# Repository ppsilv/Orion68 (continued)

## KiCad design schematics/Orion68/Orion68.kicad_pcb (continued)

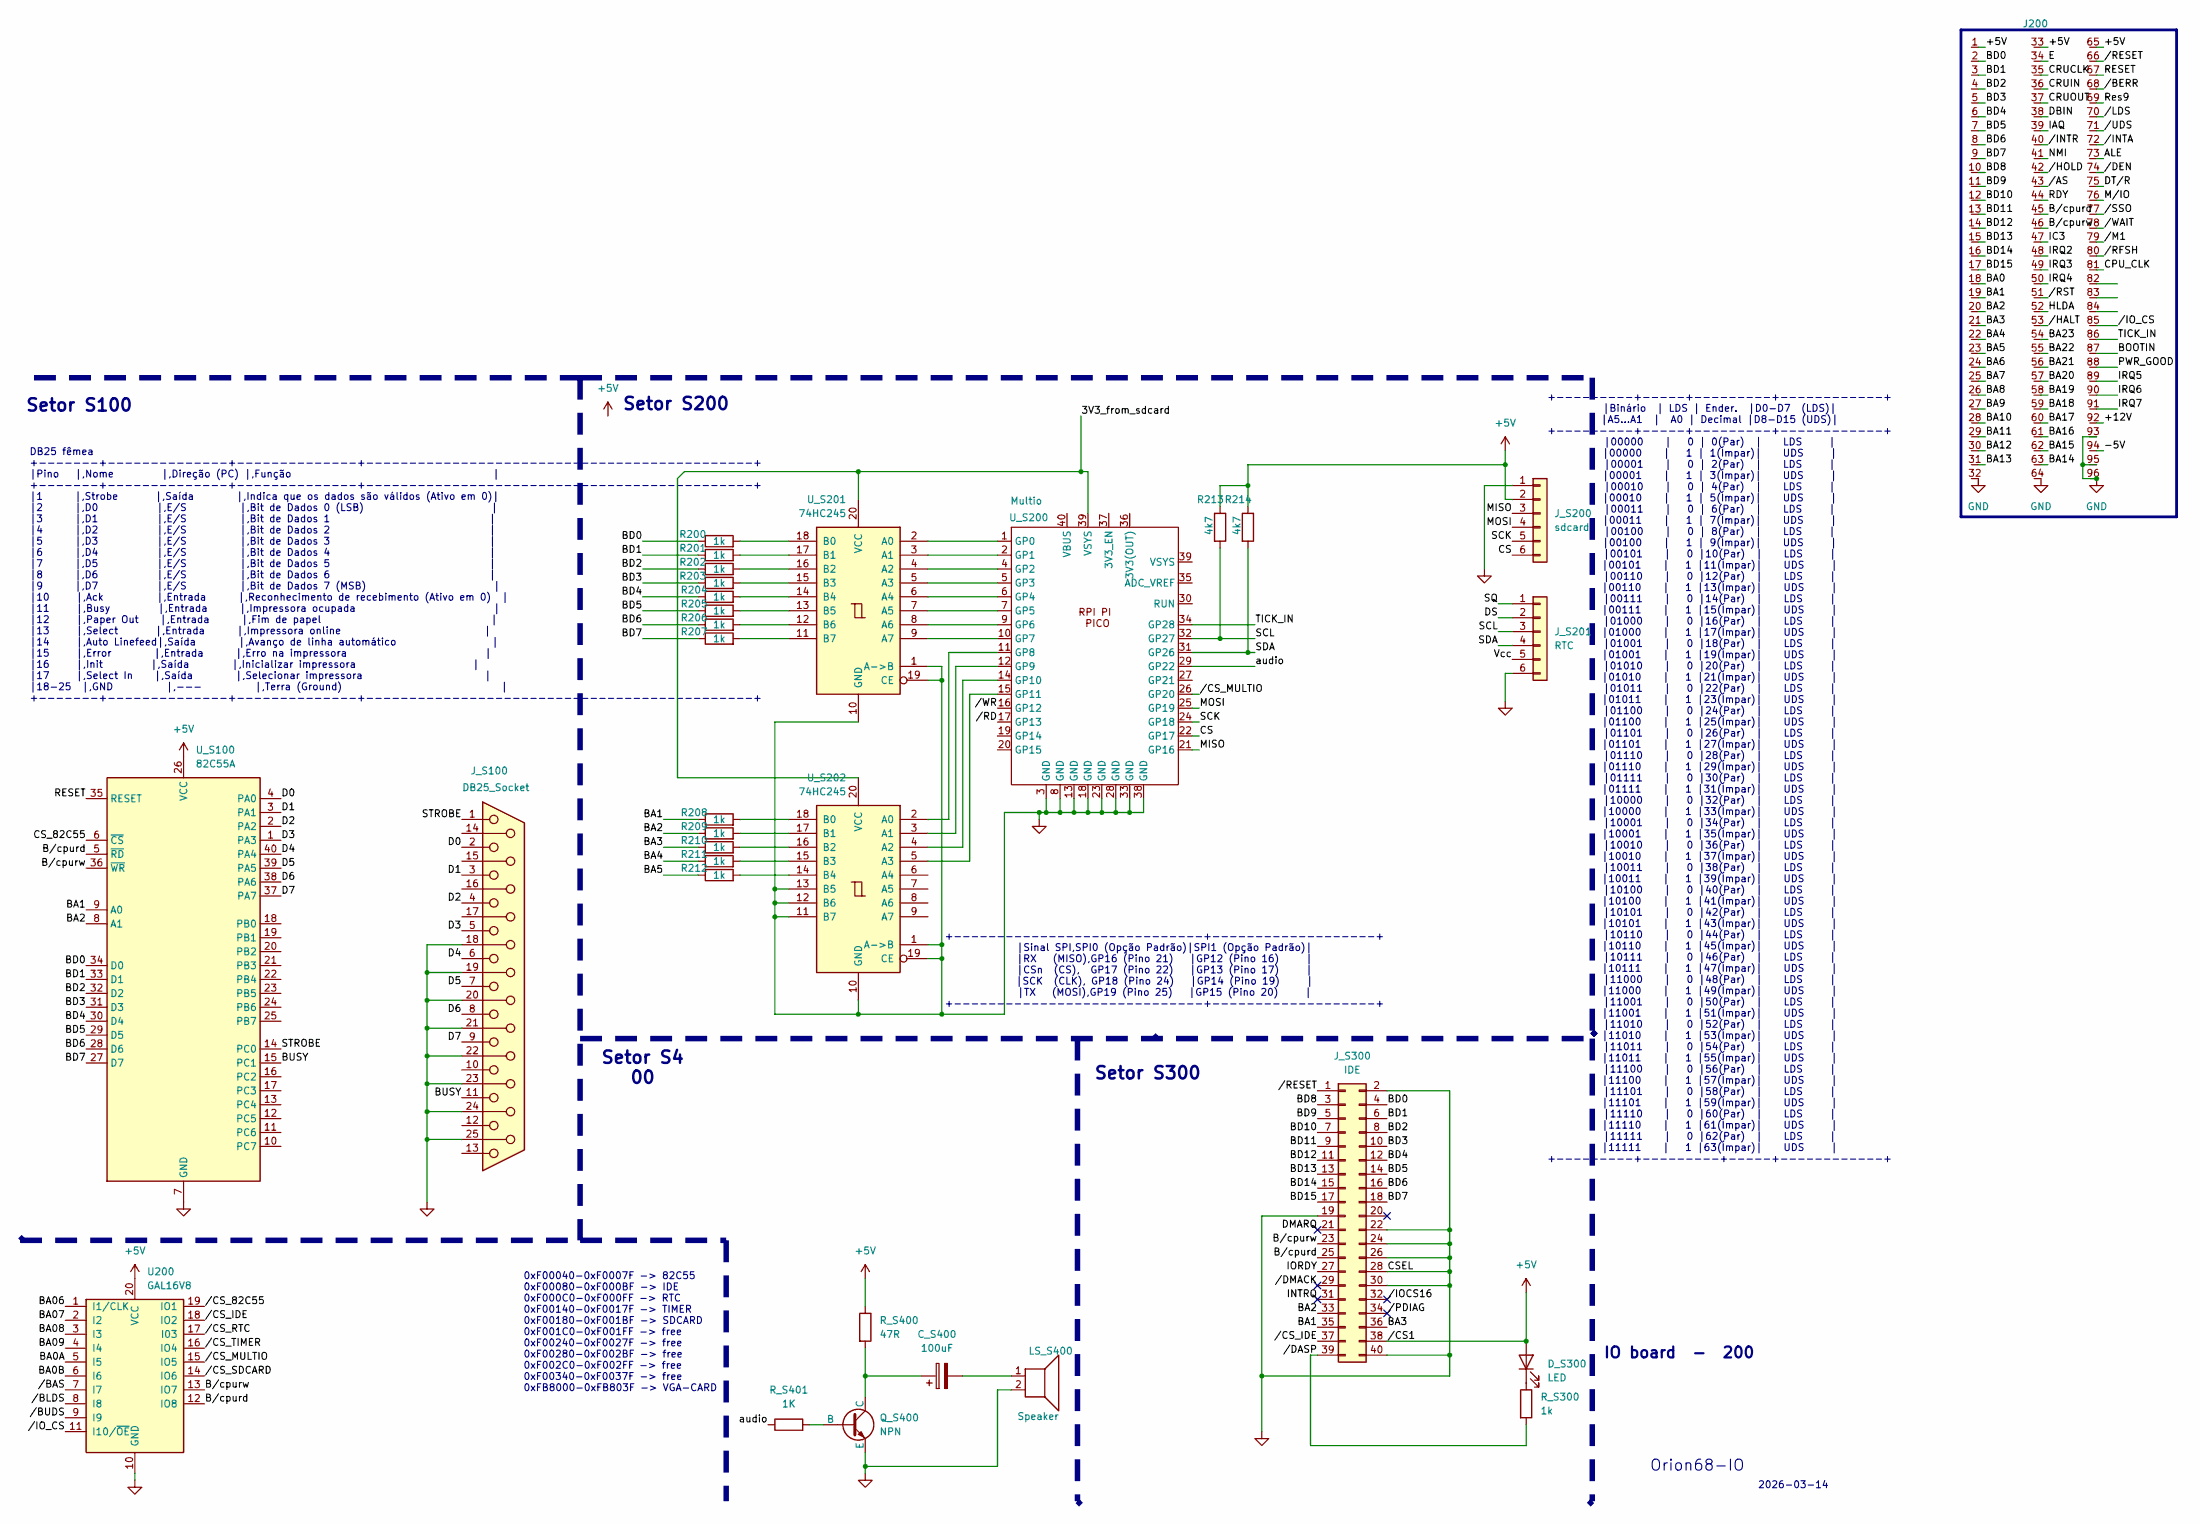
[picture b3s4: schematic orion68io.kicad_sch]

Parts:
C_S400: 100uF; CP_Radial_D5.0mm_P2.50mm
D_S300: LED; D_T-1_P5.08mm_Horizontal
J200: Euro96pin; conn_euro96
J_S100: DB25_Socket; PinHeader_2x13_P2.54mm_Vertical
J_S200: sdcard; PinSocket_1x06_P2.54mm_Vertical
J_S201: RTC; PinSocket_1x06_P2.54mm_Vertical
J_S300: IDE; PinHeader_2x20_P2.54mm_Horizontal
LS_S400: Speaker; PinHeader_1x02_P2.54mm_Vertical
Q_S400: NPN; TO-92L_Inline
R200, R201, R202, R203, R204, R205, R206, R207, R208, R209, R210, R211, R212: 1k; R_Axial_DIN0204_L3.6mm_D1.6mm_P5.08mm_Horizontal
R213, R214: 4k7; R_Axial_DIN0204_L3.6mm_D1.6mm_P5.08mm_Horizontal
R_S300: 1k; R_Axial_DIN0204_L3.6mm_D1.6mm_P5.08mm_Horizontal
R_S400: 47R; R_Axial_DIN0204_L3.6mm_D1.6mm_P5.08mm_Horizontal
R_S401: 1K; R_Axial_DIN0204_L3.6mm_D1.6mm_P5.08mm_Horizontal
U200: GAL16V8; DIP-20_W7.62mm
U_S100: 82C55A; DIP-40_W15.24mm
U_S200: Multio; DIP-40_W15.24mm
U_S201, U_S202: 74HC245; DIP-20_W7.62mm

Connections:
+5V: D_S300.2 (A), J200.1, J200.33, J200.65, J_S200.2, J_S300.38, R213.1, R214.1, R_S400.1, U200.20 (VCC), U_S100.26 (VCC); also elsewhere on the board
/Orion68-IO/3V3_from_sdcard: U_S200.39 (VSYS), U_S201.20 (VCC), U_S202.20 (VCC)
/Orion68-IO/+12V: J200.92
/Orion68-IO/-5V: J200.94
/Orion68-IO/ALE: J200.73
/Orion68-IO/BA0: J200.18
/Orion68-IO/BA0A: U200.5 (I5)
/Orion68-IO/BA0B: U200.6 (I6)
/Orion68-IO/BA1: J200.19, J_S300.35, R208.1, U_S100.9 (A0)
/Orion68-IO/BA2: J200.20, J_S300.33, R209.1, U_S100.8 (A1)
/Orion68-IO/BA3: J200.21, J_S300.36, R210.1
/Orion68-IO/BA4: J200.22, R211.1
/Orion68-IO/BA5: J200.23, R212.1
/Orion68-IO/BA06: U200.1 (I1/CLK)
/Orion68-IO/BA6: J200.24
/Orion68-IO/BA07: U200.2 (I2)
/Orion68-IO/BA7: J200.25
/Orion68-IO/BA08: U200.3 (I3)
/Orion68-IO/BA8: J200.26
/Orion68-IO/BA09: U200.4 (I4)
/Orion68-IO/BA9: J200.27
/Orion68-IO/BA10: J200.28
/Orion68-IO/BA11: J200.29
/Orion68-IO/BA12: J200.30
/Orion68-IO/BA13: J200.31
/Orion68-IO/BA14: J200.63
/Orion68-IO/BA15: J200.62
/Orion68-IO/BA16: J200.61
/Orion68-IO/BA17: J200.60
/Orion68-IO/BA18: J200.59
/Orion68-IO/BA19: J200.58
/Orion68-IO/BA20: J200.57
/Orion68-IO/BA21: J200.56
/Orion68-IO/BA22: J200.55
/Orion68-IO/BA23: J200.54
/Orion68-IO/BD0: J200.2, J_S300.4, R200.1, U_S100.34 (D0)
/Orion68-IO/BD1: J200.3, J_S300.6, R201.1, U_S100.33 (D1)
/Orion68-IO/BD2: J200.4, J_S300.8, R202.1, U_S100.32 (D2)
/Orion68-IO/BD3: J200.5, J_S300.10, R203.1, U_S100.31 (D3)
/Orion68-IO/BD4: J200.6, J_S300.12, R204.1, U_S100.30 (D4)
/Orion68-IO/BD5: J200.7, J_S300.14, R205.1, U_S100.29 (D5)
/Orion68-IO/BD6: J200.8, J_S300.16, R206.1, U_S100.28 (D6)
/Orion68-IO/BD7: J200.9, J_S300.18, R207.1, U_S100.27 (D7)
/Orion68-IO/BD8: J200.10, J_S300.3
/Orion68-IO/BD9: J200.11, J_S300.5
/Orion68-IO/BD10: J200.12, J_S300.7
/Orion68-IO/BD11: J200.13, J_S300.9
/Orion68-IO/BD12: J200.14, J_S300.11
/Orion68-IO/BD13: J200.15, J_S300.13
/Orion68-IO/BD14: J200.16, J_S300.15
/Orion68-IO/BD15: J200.17, J_S300.17
/Orion68-IO/BOOTIN: J200.87
/Orion68-IO/BUSY: J_S100.11, U_S100.15 (PC1)
/Orion68-IO/B/cpurd: J200.45, J_S300.25, U200.12 (IO8), U_S100.5 (~RD)
/Orion68-IO/B/cpurw: J200.46, J_S300.23, U200.13 (IO7), U_S100.36 (~WR)
/Orion68-IO/CPU_CLK: J200.81
/Orion68-IO/CRUCLK: J200.35
/Orion68-IO/CRUIN: J200.36
/Orion68-IO/CRUOUT: J200.37
/Orion68-IO/CS: J_S200.6, U_S200.22 (GP17)
/Orion68-IO/CS_82C55: U_S100.6 (~CS)
/Orion68-IO/D0: J_S100.2, U_S100.4 (PA0)
/Orion68-IO/D1: J_S100.3, U_S100.3 (PA1)
/Orion68-IO/D2: J_S100.4, U_S100.2 (PA2)
/Orion68-IO/D3: J_S100.5, U_S100.1 (PA3)
/Orion68-IO/D4: J_S100.6, U_S100.40 (PA4)
/Orion68-IO/D5: J_S100.7, U_S100.39 (PA5)
/Orion68-IO/D6: J_S100.8, U_S100.38 (PA6)
/Orion68-IO/D7: J_S100.9, U_S100.37 (PA7)
/Orion68-IO/DBIN: J200.38
/Orion68-IO/DMARQ: J_S300.21
/Orion68-IO/DS: J_S201.2
/Orion68-IO/DT/R: J200.75
/Orion68-IO/E: J200.34
/Orion68-IO/HLDA: J200.52
/Orion68-IO/IAQ: J200.39
/Orion68-IO/IC3: J200.47
/Orion68-IO/INTRQ: J_S300.31
/Orion68-IO/IORDY: J_S300.27
/Orion68-IO/IRQ2: J200.48
/Orion68-IO/IRQ3: J200.49
/Orion68-IO/IRQ4: J200.50
/Orion68-IO/IRQ5: J200.89
/Orion68-IO/IRQ6: J200.90
/Orion68-IO/IRQ7: J200.91
/Orion68-IO/MISO: J_S200.3, U_S200.21 (GP16)
/Orion68-IO/MOSI: J_S200.4, U_S200.25 (GP19)
/Orion68-IO/M/IO: J200.76
/Orion68-IO/NMI: J200.41
/Orion68-IO/PWR_GOOD: J200.88
/Orion68-IO/RDY: J200.44
/Orion68-IO/RESET: J200.67, U_S100.35 (RESET)
/Orion68-IO/Res9: J200.69
/Orion68-IO/SCK: J_S200.5, U_S200.24 (GP18)
/Orion68-IO/SCL: J_S201.3, R213.2, U_S200.32 (GP27)
/Orion68-IO/SDA: J_S201.4, R214.2, U_S200.31 (GP26)
/Orion68-IO/SQ: J_S201.1
/Orion68-IO/STROBE: J_S100.1, U_S100.14 (PC0)
/Orion68-IO/TICK_IN: J200.86, U_S200.34 (GP28)
/Orion68-IO/Vcc: J_S201.5
/Orion68-IO/audio: R_S401.1, U_S200.29 (GP22)
/Orion68-IO//AS: J200.43
/Orion68-IO//BAS: U200.7 (I7)
/Orion68-IO//BERR: J200.68
/Orion68-IO//BLDS: U200.8 (I8)
/Orion68-IO//BUDS: U200.9 (I9)
/Orion68-IO//CS_82C55: U200.19 (IO1)
/Orion68-IO//CS_IDE: J_S300.37, U200.18 (IO2)
/Orion68-IO//CS_MULTIO: U200.15 (IO5), U_S200.26 (GP20)
/Orion68-IO//CS_RTC: U200.17 (I03)
/Orion68-IO//CS_SDCARD: U200.14 (IO6)
/Orion68-IO//CS_TIMER: U200.16 (IO4)
/Orion68-IO//DASP: J_S300.39, R_S300.2
/Orion68-IO//DEN: J200.74
/Orion68-IO//DMACK: J_S300.29
/Orion68-IO//HALT: J200.53
/Orion68-IO//HOLD: J200.42
/Orion68-IO//INTA: J200.72
/Orion68-IO//INTR: J200.40
/Orion68-IO//IOCS16: J_S300.32
/Orion68-IO//IO_CS: J200.85, U200.11 (I10/~OE)
/Orion68-IO//LDS: J200.70
/Orion68-IO//M1: J200.79
/Orion68-IO//PDIAG: J_S300.34
/Orion68-IO//RD: U_S200.17 (GP13)
/Orion68-IO//RESET: J200.66, J_S300.1
/Orion68-IO//RFSH: J200.80
/Orion68-IO//RST: J200.51
/Orion68-IO//SSO: J200.77
/Orion68-IO//UDS: J200.71
/Orion68-IO//WAIT: J200.78
/Orion68-IO//WR: U_S200.16 (GP12)
GND: J200.32, J200.64, J200.93, J200.95, J200.96, J_S100.18, J_S100.19, J_S100.20, J_S100.21, J_S100.22, J_S100.23, J_S100.24, J_S100.25, J_S200.1, J_S201.6, J_S300.2, J_S300.19, J_S300.22, J_S300.24, J_S300.26, J_S300.28, J_S300.30, J_S300.40, LS_S400.2, Q_S400.3 (E), U200.10 (GND), U_S100.7 (GND), U_S200.3 (GND), U_S200.8 (GND), U_S200.13 (GND), U_S200.18 (GND), U_S200.23 (GND), U_S200.28 (GND), U_S200.33 (GND), U_S200.38 (GND), U_S201.1 (A->B), U_S201.10 (GND), U_S201.19 (CE), U_S202.1 (A->B), U_S202.10 (GND), U_S202.11 (B7), U_S202.12 (B6), U_S202.13 (B5), U_S202.19 (CE); also elsewhere on the board
unnamed: C_S400.2, LS_S400.1
unnamed: D_S300.1 (K), R_S300.1
unnamed: Q_S400.2 (B), R_S401.2
unnamed: C_S400.1, Q_S400.1 (C), R_S400.2
unnamed: U_S200.1 (GP0), U_S201.2 (A0)
unnamed: U_S200.2 (GP1), U_S201.3 (A1)
unnamed: U_S200.4 (GP2), U_S201.4 (A2)
unnamed: U_S200.5 (GP3), U_S201.5 (A3)
unnamed: U_S200.6 (GP4), U_S201.6 (A4)
unnamed: U_S200.7 (GP5), U_S201.7 (A5)
unnamed: U_S200.9 (GP6), U_S201.8 (A6)
unnamed: U_S200.10 (GP7), U_S201.9 (A7)
unnamed: U_S200.11 (GP8), U_S202.2 (A0)
unnamed: U_S200.12 (GP9), U_S202.3 (A1)
unnamed: U_S200.14 (GP10), U_S202.4 (A2)
unnamed: U_S200.15 (GP11), U_S202.5 (A3)
unnamed: R200.2, U_S201.18 (B0)
unnamed: R201.2, U_S201.17 (B1)
unnamed: R202.2, U_S201.16 (B2)
unnamed: R203.2, U_S201.15 (B3)
unnamed: R204.2, U_S201.14 (B4)
unnamed: R205.2, U_S201.13 (B5)
unnamed: R206.2, U_S201.12 (B6)
unnamed: R207.2, U_S201.11 (B7)
unnamed: R208.2, U_S202.18 (B0)
unnamed: R209.2, U_S202.17 (B1)
unnamed: R210.2, U_S202.16 (B2)
unnamed: R211.2, U_S202.15 (B3)
unnamed: R212.2, U_S202.14 (B4)

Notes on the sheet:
2026-03-14
Setor S4 00
+---------+-----+---------+------------+ |Binário | LDS | Ender. |D0-D7 (LDS)| |A5...A1 | A0 | Decimal |D8-D15 (UDS)| +---------+-----+---------+------------+ |00000 | 0 | 0(Par) | LDS | |00000 | 1 | 1(Ímpar)| UDS | |00001 | 0 | 2(Par) | LDS | |00001 | 1 | 3(Ímpar)| UDS | |00010 | 0 | 4(Par) | LDS 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
DB25 fêmea +-------+--------------+--------------+---------------------------------------------+ |Pino |,Nome |,Direção (PC) |,Função | +-------+--------------+--------------+---------------------------------------------+ |1 |,Strobe |,Saída |,Indica que os dados são válidos (Ativo em 0)| |2 |,D0 |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
IO board - 200
Orion68-IO
Setor S100
Setor S200
0xF00040-0xF0007F -> 82C55 0xF00080-0xF000BF -> IDE 0xF000C0-0xF000FF -> RTC 0xF00140-0xF0017F -> TIMER 0xF00180-0xF001BF -> SDCARD 0xF001C0-0xF001FF -> free 0xF00240-0xF0027F -> free 0xF00280-0xF002BF -> free 0xF002C0-0xF002FF -> free 0xF00340-0xF0037F -> free 0xFB8000-0xFB803F -> VGA-CARD
+-----------------------------+-------------------+ |Sinal SPI,SPI0 (Opção Padrão)|SPI1 (Opção Padrão)| |RX (MISO),GP16 (Pino 21) |GP12 (Pino 16) | |CSn (CS), GP17 (Pino 22) |GP13 (Pino 17) | |SCK (CLK), GP18 (Pino 24) |GP14 (Pino 19) | |TX (MOSI),GP19 (Pino 25) |GP15 (Pino 20) | +-----------------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
Setor S300

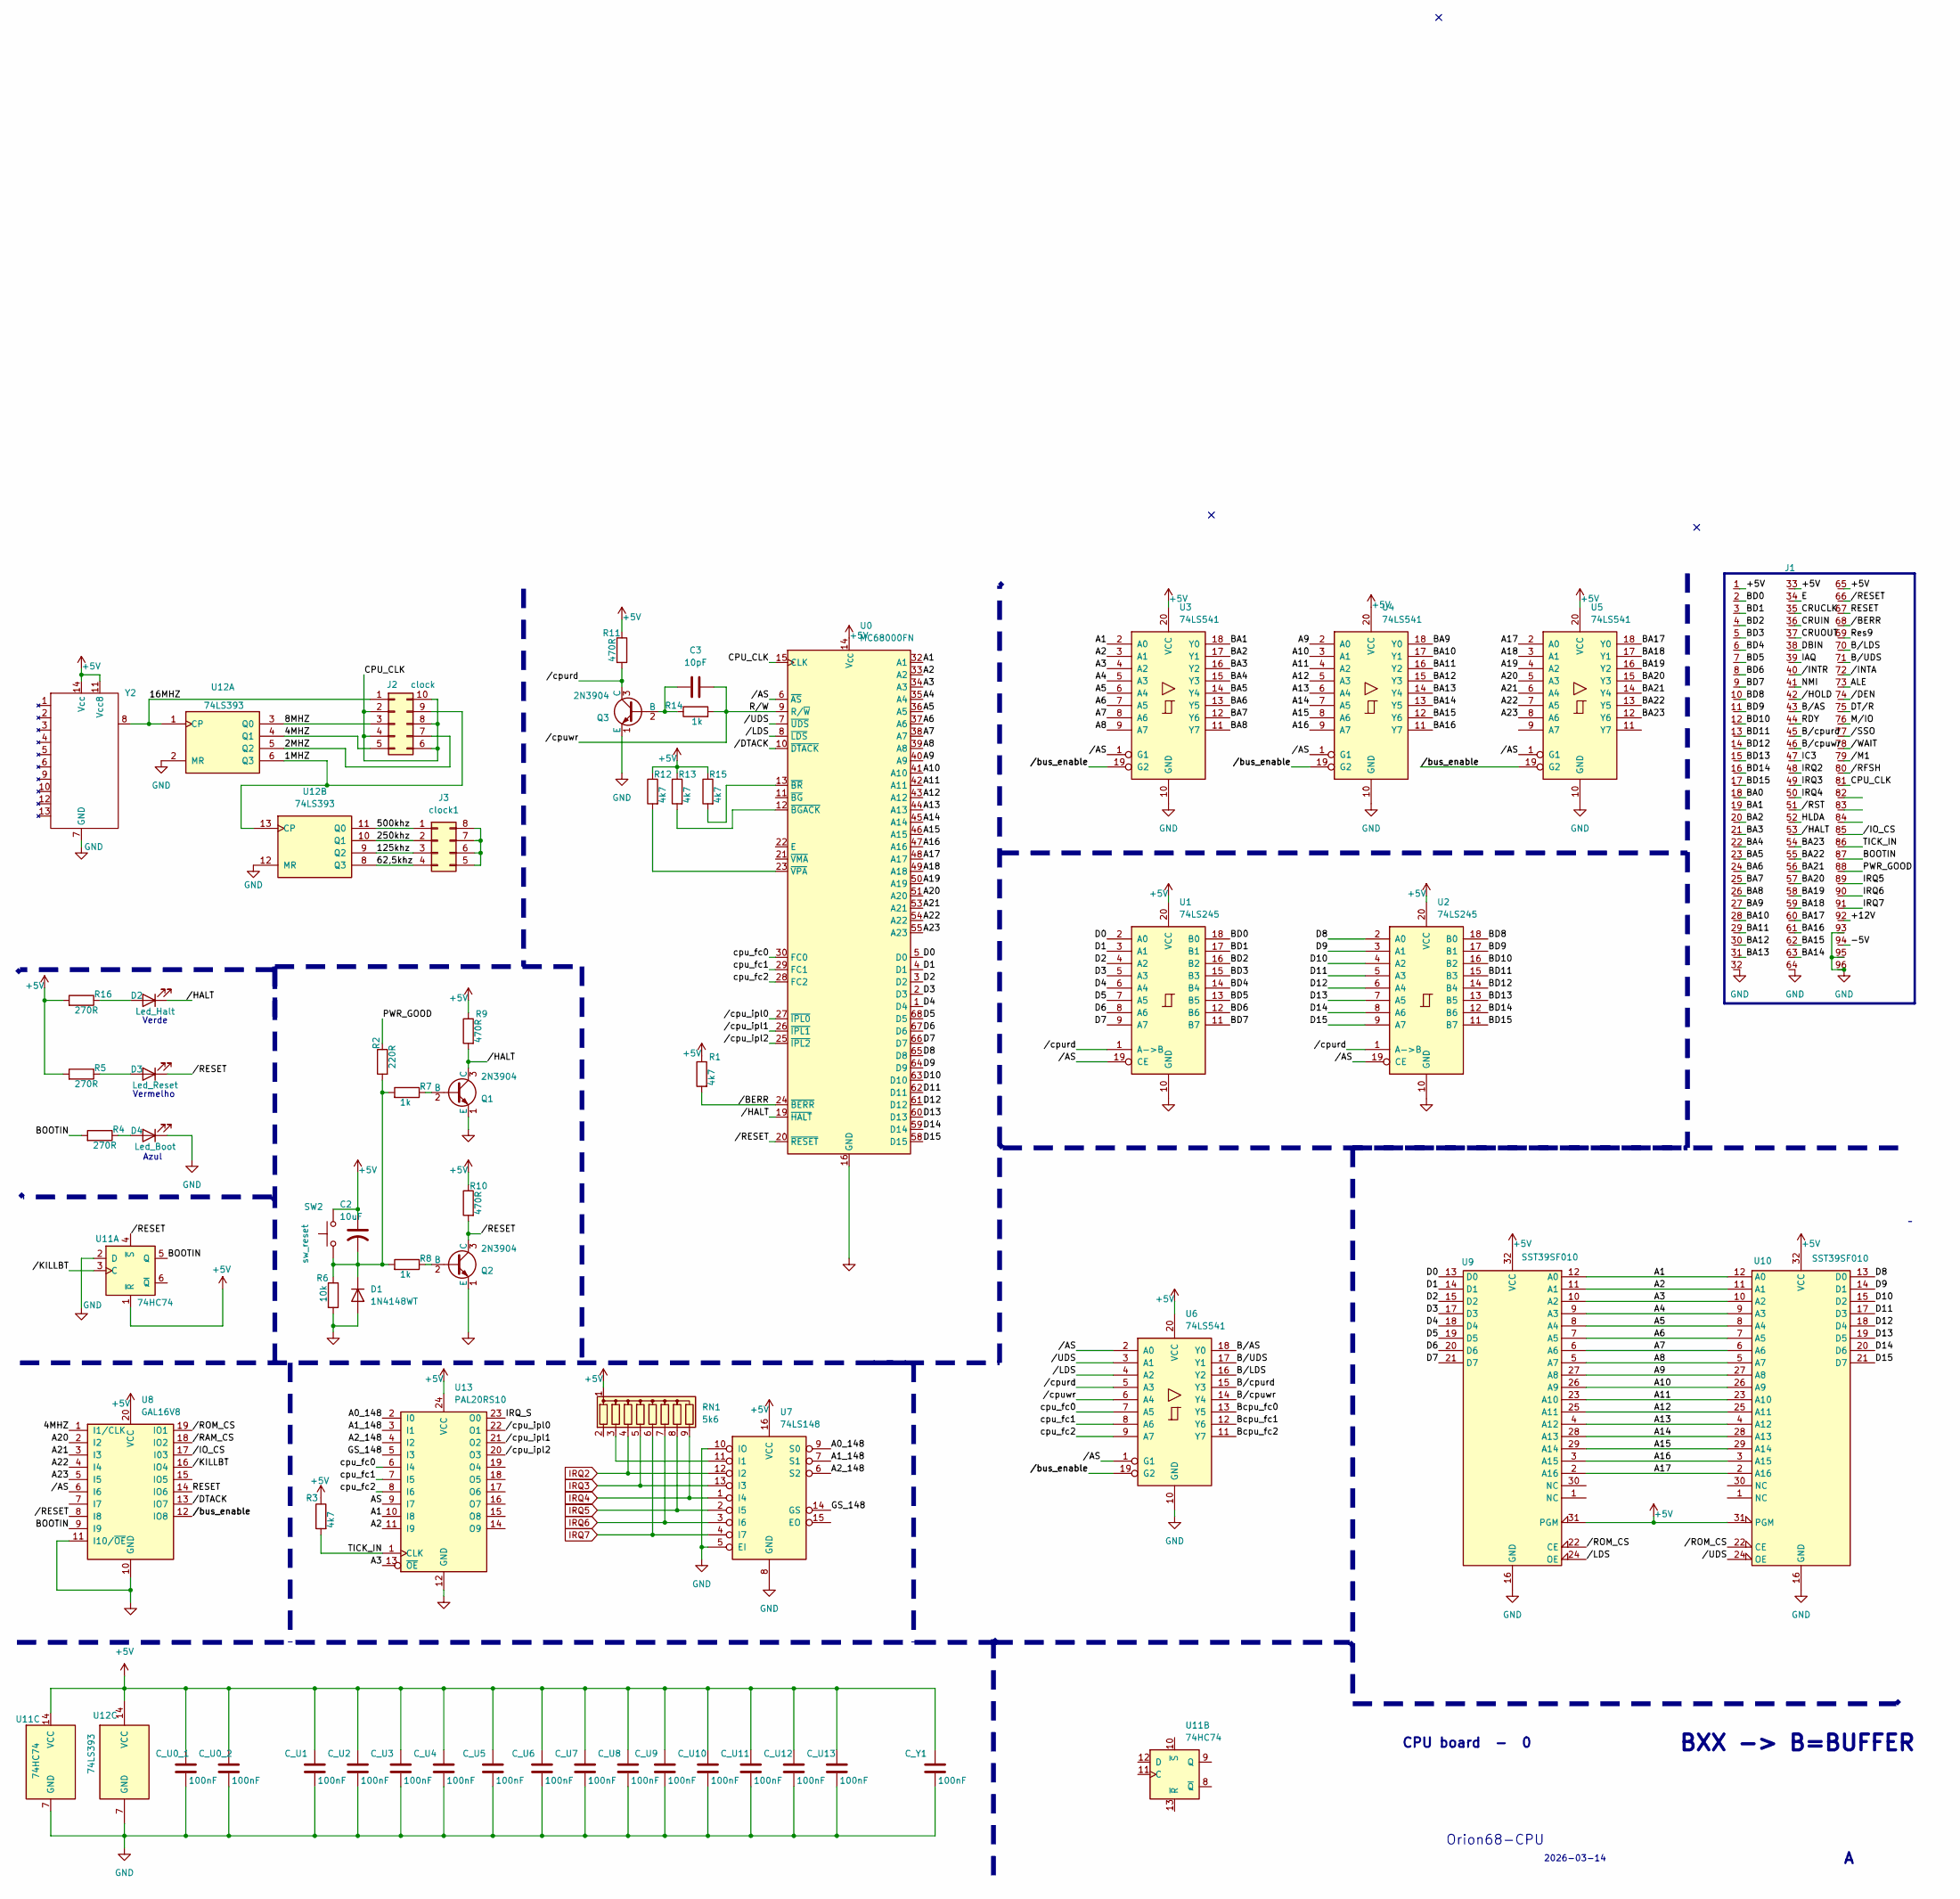
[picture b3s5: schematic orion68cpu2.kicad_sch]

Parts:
C2: 10uF; CP_Radial_D5.0mm_P2.50mm
C3: 10pF; C_Disc_D4.3mm_W1.9mm_P5.00mm
C_U0_1, C_U0_2, C_U1, C_U2, C_U3, C_U4, C_U5, C_U6, C_U7, C_U8, C_U9, C_U10, C_U11, C_U12, C_U13: 100nF; C_Disc_D4.3mm_W1.9mm_P5.00mm
C_Y1: 100nF; C_Disc_D4.3mm_W1.9mm_P5.00mm
D1: 1N4148WT; D_T-1_P5.08mm_Horizontal
D2: Led_Halt; D_T-1_P5.08mm_Horizontal
D3: Led_Reset; D_T-1_P5.08mm_Horizontal
D4: Led_Boot; D_T-1_P5.08mm_Horizontal
J1: Euro96pin; conn_euro96
J2: clock; PinHeader_2x05_P2.54mm_Vertical
J3: clock1; PinHeader_2x04_P2.54mm_Vertical
Q1, Q2, Q3: 2N3904; TO-92_Inline
R1, R3, R12, R13, R15: 4k7; R_Axial_DIN0204_L3.6mm_D1.6mm_P5.08mm_Horizontal
R2: 220R; R_Axial_DIN0204_L3.6mm_D1.6mm_P5.08mm_Horizontal
R4, R5, R16: 270R; R_Axial_DIN0204_L3.6mm_D1.6mm_P5.08mm_Horizontal
R6: 10k; R_Axial_DIN0204_L3.6mm_D1.6mm_P5.08mm_Horizontal
R7, R8, R14: 1k; R_Axial_DIN0204_L3.6mm_D1.6mm_P5.08mm_Horizontal
R9, R10, R11: 470R; R_Axial_DIN0204_L3.6mm_D1.6mm_P5.08mm_Horizontal
RN1: 5k6; R_Array_SIP9
SW2: sw_reset; SW_Lever_1P2T_NKK_GW12LxH
U0: MC68000FN; PLCC-68_THT-Socket
U1, U2: 74LS245; DIP-20_W7.62mm
U3, U4, U5, U6: 74LS541; DIP-20_W7.62mm
U7: 74LS148; DIP-16_W7.62mm
U8: GAL16V8; DIP-20_W7.62mm
U9, U10: SST39SF010; PLCC-32_THT-Socket
U11: 74HC74; DIP-14_W7.62mm
U12: 74LS393; DIP-14_W7.62mm
U13: PAL20RS10; DIP-24_W7.62mm
Y2: DIP-14_W7.62mm

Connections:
+5V: C2.1, C_U0_1.1, C_U0_2.1, C_U1.1, C_U2.1, C_U3.1, C_U4.1, C_U5.1, C_U6.1, C_U7.1, C_U8.1, C_U9.1, C_U10.1, C_U11.1, C_U12.1, C_U13.1, C_Y1.1, J1.1, J1.33, J1.65, R1.1, R3.1, R5.2, R9.1, R10.1, R11.1, R12.1, R13.1, R15.1, R16.2, RN1.1 (common), SW2.2, U0.14 (V_{CC}), U0.52 (V_{CC}), U1.20 (VCC), U2.20 (VCC), U3.20 (VCC), U4.20 (VCC), U5.20 (VCC), U6.20 (VCC), U7.16 (VCC), U8.20 (VCC), U9.31 (PGM), U9.32 (VCC), U10.31 (PGM), U10.32 (VCC), U11.1 (~R), U11.14 (VCC), U12.14 (VCC), U13.24 (VCC), Y2.11 (Vcc8), Y2.14 (Vcc); also elsewhere on the board
/Orion68-CPU-2/1MHZ: J2.9, U12.6 (Q3), U12.13 (CP)
/Orion68-CPU-2/2MHZ: J2.7, U12.5 (Q2)
/Orion68-CPU-2/4MHZ: J2.5, U8.1 (I1/CLK), U12.4 (Q1)
/Orion68-CPU-2/8MHZ: J2.3, U12.3 (Q0)
/Orion68-CPU-2/16MHZ: J2.1, U12.1 (CP), Y2.8
/Orion68-CPU-2/62,5khz: J3.4, U12.8 (Q3)
/Orion68-CPU-2/125khz: J3.3, U12.9 (Q2)
/Orion68-CPU-2/250khz: J3.2, U12.10 (Q1)
/Orion68-CPU-2/500khz: J3.1, U12.11 (Q0)
/Orion68-CPU-2/+12V: J1.92
/Orion68-CPU-2/-5V: J1.94
/Orion68-CPU-2/<NO NET>: U0.26 (~IPL1), U13.21 (O2)
/Orion68-CPU-2/A0_148: U7.9 (S0), U13.2 (I0)
/Orion68-CPU-2/A1: U0.32 (A1), U3.2 (A0), U9.12 (A0), U10.12 (A0), U13.10 (I8)
/Orion68-CPU-2/A1_148: U7.7 (S1), U13.3 (I1)
/Orion68-CPU-2/A2: U0.33 (A2), U3.3 (A1), U9.11 (A1), U10.11 (A1), U13.11 (I9)
/Orion68-CPU-2/A2_148: U7.6 (S2), U13.4 (I2)
/Orion68-CPU-2/A3: U0.34 (A3), U3.4 (A2), U9.10 (A2), U10.10 (A2), U13.13 (~OE)
/Orion68-CPU-2/A4: U0.35 (A4), U3.5 (A3), U9.9 (A3), U10.9 (A3)
/Orion68-CPU-2/A5: U0.36 (A5), U3.6 (A4), U9.8 (A4), U10.8 (A4)
/Orion68-CPU-2/A6: U0.37 (A6), U3.7 (A5), U9.7 (A5), U10.7 (A5)
/Orion68-CPU-2/A7: U0.38 (A7), U3.8 (A6), U9.6 (A6), U10.6 (A6)
/Orion68-CPU-2/A8: U0.39 (A8), U3.9 (A7), U9.5 (A7), U10.5 (A7)
/Orion68-CPU-2/A9: U0.40 (A9), U4.2 (A0), U9.27 (A8), U10.27 (A8)
/Orion68-CPU-2/A10: U0.41 (A10), U4.3 (A1), U9.26 (A9), U10.26 (A9)
/Orion68-CPU-2/A11: U0.42 (A11), U4.4 (A2), U9.23 (A10), U10.23 (A10)
/Orion68-CPU-2/A12: U0.43 (A12), U4.5 (A3), U9.25 (A11), U10.25 (A11)
/Orion68-CPU-2/A13: U0.44 (A13), U4.6 (A4), U9.4 (A12), U10.4 (A12)
/Orion68-CPU-2/A14: U0.45 (A14), U4.7 (A5), U9.28 (A13), U10.28 (A13)
/Orion68-CPU-2/A15: U0.46 (A15), U4.8 (A6), U9.29 (A14), U10.29 (A14)
/Orion68-CPU-2/A16: U0.47 (A16), U4.9 (A7), U9.3 (A15), U10.3 (A15)
/Orion68-CPU-2/A17: U0.48 (A17), U5.2 (A0), U9.2 (A16), U10.2 (A16)
/Orion68-CPU-2/A18: U0.49 (A18), U5.3 (A1)
/Orion68-CPU-2/A19: U0.50 (A19), U5.4 (A2)
/Orion68-CPU-2/A20: U0.51 (A20), U5.5 (A3), U8.2 (I2)
/Orion68-CPU-2/A21: U0.53 (A21), U5.6 (A4), U8.3 (I3)
/Orion68-CPU-2/A22: U0.54 (A22), U5.7 (A5), U8.4 (I4)
/Orion68-CPU-2/A23: U0.55 (A23), U5.8 (A6), U8.5 (I5)
/Orion68-CPU-2/ALE: J1.73
/Orion68-CPU-2/AS: U13.9 (I7)
/Orion68-CPU-2/BA0: J1.18
/Orion68-CPU-2/BA1: J1.19, U3.18 (Y0)
/Orion68-CPU-2/BA2: J1.20, U3.17 (Y1)
/Orion68-CPU-2/BA3: J1.21, U3.16 (Y2)
/Orion68-CPU-2/BA4: J1.22, U3.15 (Y3)
/Orion68-CPU-2/BA5: J1.23, U3.14 (Y4)
/Orion68-CPU-2/BA6: J1.24, U3.13 (Y5)
/Orion68-CPU-2/BA7: J1.25, U3.12 (Y6)
/Orion68-CPU-2/BA8: J1.26, U3.11 (Y7)
/Orion68-CPU-2/BA9: J1.27, U4.18 (Y0)
/Orion68-CPU-2/BA10: J1.28, U4.17 (Y1)
/Orion68-CPU-2/BA11: J1.29, U4.16 (Y2)
/Orion68-CPU-2/BA12: J1.30, U4.15 (Y3)
/Orion68-CPU-2/BA13: J1.31, U4.14 (Y4)
/Orion68-CPU-2/BA14: J1.63, U4.13 (Y5)
/Orion68-CPU-2/BA15: J1.62, U4.12 (Y6)
/Orion68-CPU-2/BA16: J1.61, U4.11 (Y7)
/Orion68-CPU-2/BA17: J1.60, U5.18 (Y0)
/Orion68-CPU-2/BA18: J1.59, U5.17 (Y1)
/Orion68-CPU-2/BA19: J1.58, U5.16 (Y2)
/Orion68-CPU-2/BA20: J1.57, U5.15 (Y3)
/Orion68-CPU-2/BA21: J1.56, U5.14 (Y4)
/Orion68-CPU-2/BA22: J1.55, U5.13 (Y5)
/Orion68-CPU-2/BA23: J1.54, U5.12 (Y6)
/Orion68-CPU-2/BD0: J1.2, U1.18 (B0)
/Orion68-CPU-2/BD1: J1.3, U1.17 (B1)
/Orion68-CPU-2/BD2: J1.4, U1.16 (B2)
/Orion68-CPU-2/BD3: J1.5, U1.15 (B3)
/Orion68-CPU-2/BD4: J1.6, U1.14 (B4)
/Orion68-CPU-2/BD5: J1.7, U1.13 (B5)
/Orion68-CPU-2/BD6: J1.8, U1.12 (B6)
/Orion68-CPU-2/BD7: J1.9, U1.11 (B7)
/Orion68-CPU-2/BD8: J1.10, U2.18 (B0)
/Orion68-CPU-2/BD9: J1.11, U2.17 (B1)
/Orion68-CPU-2/BD10: J1.12, U2.16 (B2)
/Orion68-CPU-2/BD11: J1.13, U2.15 (B3)
/Orion68-CPU-2/BD12: J1.14, U2.14 (B4)
/Orion68-CPU-2/BD13: J1.15, U2.13 (B5)
/Orion68-CPU-2/BD14: J1.16, U2.12 (B6)
/Orion68-CPU-2/BD15: J1.17, U2.11 (B7)
/Orion68-CPU-2/BOOTIN: J1.87, R4.2, U8.9 (I9), U11.5 (Q)
/Orion68-CPU-2/Bcpu_fc0: U6.13 (Y5)
/Orion68-CPU-2/Bcpu_fc1: U6.12 (Y6)
/Orion68-CPU-2/Bcpu_fc2: U6.11 (Y7)
/Orion68-CPU-2/B/AS: J1.43, U6.18 (Y0)
/Orion68-CPU-2/B/LDS: J1.70, U6.16 (Y2)
/Orion68-CPU-2/B/UDS: J1.71, U6.17 (Y1)
/Orion68-CPU-2/B/cpurd: J1.45, U6.15 (Y3)
/Orion68-CPU-2/B/cpuwr: J1.46, U6.14 (Y4)
/Orion68-CPU-2/CPU_CLK: J1.81, J2.2, J2.4, J2.6, J2.8, J2.10, U0.15 (CLK)
/Orion68-CPU-2/CRUCLK: J1.35
/Orion68-CPU-2/CRUIN: J1.36
/Orion68-CPU-2/CRUOUT: J1.37
/Orion68-CPU-2/D0: U0.5 (D0), U1.2 (A0), U9.13 (D0)
/Orion68-CPU-2/D1: U0.4 (D1), U1.3 (A1), U9.14 (D1)
/Orion68-CPU-2/D2: U0.3 (D2), U1.4 (A2), U9.15 (D2)
/Orion68-CPU-2/D3: U0.2 (D3), U1.5 (A3), U9.17 (D3)
/Orion68-CPU-2/D4: U0.1 (D4), U1.6 (A4), U9.18 (D4)
/Orion68-CPU-2/D5: U0.68 (D5), U1.7 (A5), U9.19 (D5)
/Orion68-CPU-2/D6: U0.67 (D6), U1.8 (A6), U9.20 (D6)
/Orion68-CPU-2/D7: U0.66 (D7), U1.9 (A7), U9.21 (D7)
/Orion68-CPU-2/D8: U0.65 (D8), U2.2 (A0), U10.13 (D0)
/Orion68-CPU-2/D9: U0.64 (D9), U2.3 (A1), U10.14 (D1)
/Orion68-CPU-2/D10: U0.63 (D10), U2.4 (A2), U10.15 (D2)
/Orion68-CPU-2/D11: U0.62 (D11), U2.5 (A3), U10.17 (D3)
/Orion68-CPU-2/D12: U0.61 (D12), U2.6 (A4), U10.18 (D4)
/Orion68-CPU-2/D13: U0.60 (D13), U2.7 (A5), U10.19 (D5)
/Orion68-CPU-2/D14: U0.59 (D14), U2.8 (A6), U10.20 (D6)
/Orion68-CPU-2/D15: U0.58 (D15), U2.9 (A7), U10.21 (D7)
/Orion68-CPU-2/DBIN: J1.38
/Orion68-CPU-2/DT/R: J1.75
/Orion68-CPU-2/E: J1.34
/Orion68-CPU-2/GS_148: U7.14 (GS), U13.5 (I3)
/Orion68-CPU-2/HLDA: J1.52
/Orion68-CPU-2/IAQ: J1.39
/Orion68-CPU-2/IC3: J1.47
/Orion68-CPU-2/IRQ_S: U13.23 (O0)
/Orion68-CPU-2/M/IO: J1.76
/Orion68-CPU-2/NMI: J1.41
/Orion68-CPU-2/PWR_GOOD: J1.88, R2.1
/Orion68-CPU-2/RDY: J1.44
/Orion68-CPU-2/RESET: J1.67, U8.14 (IO6)
/Orion68-CPU-2/Res9: J1.69
/Orion68-CPU-2/R/W: C3.2, R14.2, U0.9 (R/~W), U6.6 (A4)
/Orion68-CPU-2/TICK_IN: J1.86, R3.2, U13.1 (CLK)
/Orion68-CPU-2/cpu_fc0: U0.30 (FC0), U6.7 (A5), U13.6 (I4)
/Orion68-CPU-2/cpu_fc1: U0.29 (FC1), U6.8 (A6), U13.7 (I5)
/Orion68-CPU-2/cpu_fc2: U0.28 (FC2), U6.9 (A7), U13.8 (I6)
/Orion68-CPU-2//AS: U0.6 (~AS), U1.19 (CE), U2.19 (CE), U3.1 (G1), U4.1 (G1), U5.1 (G1), U6.1 (G1), U6.2 (A0), U8.6 (I6)
/Orion68-CPU-2//BERR: J1.68, R1.2, U0.24 (~BERR)
/Orion68-CPU-2//DEN: J1.74
/Orion68-CPU-2//DTACK: U0.10 (~DTACK), U8.13 (IO7)
/Orion68-CPU-2//HALT: D2.1 (K), J1.53, Q1.3 (C), R9.2, U0.19 (~HALT)
/Orion68-CPU-2//HOLD: J1.42
/Orion68-CPU-2//INTA: J1.72
/Orion68-CPU-2//INTR: J1.40
/Orion68-CPU-2//IO_CS: J1.85, U8.17 (I03)
/Orion68-CPU-2//KILLBT: U8.16 (IO4), U11.3 (C)
/Orion68-CPU-2//LDS: U0.8 (~LDS), U6.4 (A2), U9.24 (OE)
/Orion68-CPU-2//M1: J1.79
/Orion68-CPU-2//RAM_CS: U8.18 (IO2)
/Orion68-CPU-2//RESET: D3.1 (K), J1.66, Q2.3 (C), R10.2, U0.20 (~RESET), U8.8 (I8), U11.4 (~S)
/Orion68-CPU-2//RFSH: J1.80
/Orion68-CPU-2//ROM_CS: U8.19 (IO1), U9.22 (CE), U10.22 (CE)
/Orion68-CPU-2//RST: J1.51
/Orion68-CPU-2//SSO: J1.77
/Orion68-CPU-2//UDS: U0.7 (~UDS), U6.3 (A1), U10.24 (OE)
/Orion68-CPU-2//WAIT: J1.78
/Orion68-CPU-2//bus_enable: U3.19 (G2), U4.19 (G2), U5.19 (G2), U6.19 (G2), U8.12 (IO8)
/Orion68-CPU-2//cpu_ipl0: U0.27 (~IPL0), U13.22 (O1)
/Orion68-CPU-2//cpu_ipl2: U0.25 (~IPL2), U13.20 (O3)
/Orion68-CPU-2//cpurd: Q3.3 (C), R11.2, U1.1 (A->B), U2.1 (A->B), U6.5 (A3)
GND: C_U0_1.2, C_U0_2.2, C_U1.2, C_U2.2, C_U3.2, C_U4.2, C_U5.2, C_U6.2, C_U7.2, C_U8.2, C_U9.2, C_U10.2, C_U11.2, C_U12.2, C_U13.2, C_Y1.2, D1.2 (A), D4.1 (K), J1.32, J1.64, J1.93, J1.95, J1.96, Q1.1 (E), Q2.1 (E), Q3.1 (E), R6.2, U0.16 (GND), U0.17 (GND), U0.56 (GND), U0.57 (GND), U1.10 (GND), U2.10 (GND), U3.10 (GND), U4.10 (GND), U5.10 (GND), U6.10 (GND), U7.5 (EI), U7.8 (GND), U7.10 (IO), U8.10 (GND), U8.11 (I10/~OE), U9.16 (GND), U10.16 (GND), U11.2 (D), U11.7 (GND), U12.2 (MR), U12.7 (GND), U12.12 (MR), U13.12 (GND), Y2.7 (GND); also elsewhere on the board
IRQ2: J1.48, RN1.4 (R3), U7.12 (I2)
IRQ3: J1.49, RN1.5 (R4), U7.13 (I3)
IRQ4: J1.50, RN1.9 (R8), U7.1 (I4)
IRQ5: J1.89, RN1.8 (R7), U7.2 (I5)
IRQ6: J1.90, RN1.7 (R6), U7.3 (I6)
IRQ7: J1.91, RN1.6 (R5), U7.4 (I7)
unnamed: C2.2, D1.1 (K), R2.2, R6.1, R7.2, R8.2, SW2.1
unnamed: D2.2 (A), R16.1
unnamed: D3.2 (A), R5.1
unnamed: D4.2 (A), R4.1
unnamed: J3.5, J3.6, J3.7, J3.8
unnamed: Q1.2 (B), R7.1
unnamed: Q2.2 (B), R8.1
unnamed: C3.1, Q3.2 (B), R14.1
unnamed: RN1.3 (R2), U7.11 (I1)
unnamed: R13.2, U0.12 (~BGACK)
unnamed: R15.2, U0.13 (~BR)
unnamed: R12.2, U0.23 (~VPA)

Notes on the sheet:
Verde
Azul
Vermelho
CPU board - 0
BXX -> B=BUFFER
Orion68-CPU
2026-03-14

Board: 2 copper layers, 129 parts (0 on the bottom side), 328 nets, no tracks yet.

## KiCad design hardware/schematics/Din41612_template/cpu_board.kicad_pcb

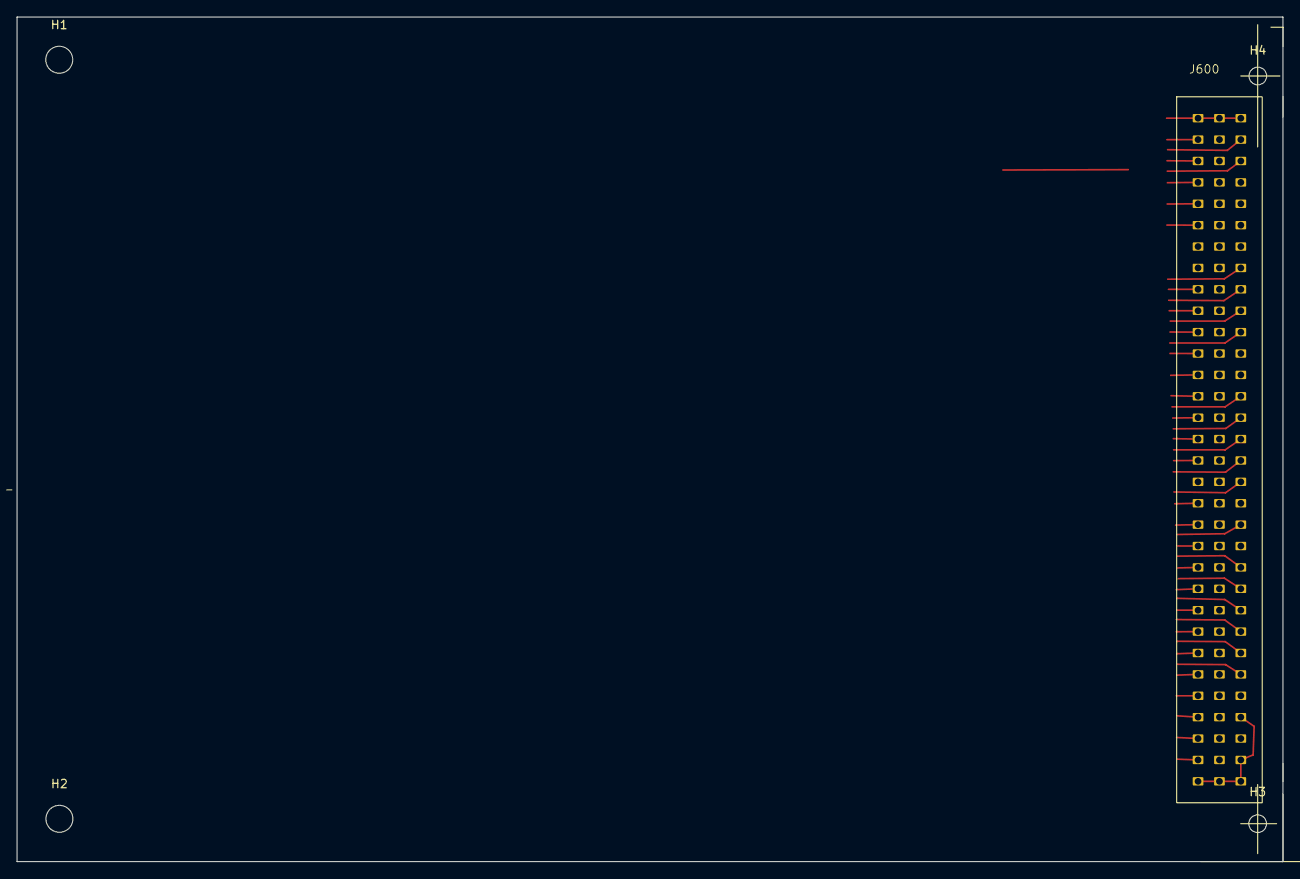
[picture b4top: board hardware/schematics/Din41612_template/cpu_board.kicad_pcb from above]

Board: 2 copper layers, 150.3 x 100.3 mm, 5 parts (0 on the bottom side), 2 nets.

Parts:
H1, H2: MountingHole; MountingHole_3.2mm_M3
H3, H4: MountingHole; MountingHole_2.1mm
J600: Euro96pin; conn_euro96

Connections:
/+5V: J600.1, J600.33, J600.65
GND: J600.32, J600.64, J600.96

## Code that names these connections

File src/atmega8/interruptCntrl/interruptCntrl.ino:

#include <avr/io.h>
#include <util/atomic.h>
#include <util/delay.h>

/*
  minipro -p  ATMEGA8@DIP28 -w interruptCntrl.ino.with_bootloader.bin
*/


//When cpu say FC0,FC1 and FC2  = 1,1,1 but no interrupt active.
#define CPU_INT_ACK_WRONG     0x80
//When arrive a irq resquest but we have one active irq in curse
#define IRQ_REQUEST_LOST      0x81
//ACK sem interrupção
#define ACK_WITHOUT_INT       0x82
//Irq <level> must be released
#define IRQ_MUST_BE_RELEASED  0x83

// Definições dos pinos IPL no PORTB
#define IPL0  PC0
#define IPL1  PC1  
#define IPL2  PC2
#define IPL_MASK ((1 << IPL0) | (1 << IPL1) | (1 << IPL2))

// Definições dos pinos de IRQ no PORTD
#define IRQ1_PIN  PD2
#define IRQ2_PIN  PD3
#define IRQ3_PIN  PD4
#define IRQ4_PIN  PD5
#define IRQ5_PIN  PD6
#define IRQ7_PIN  PD7
#define ALL_IRQ_MASK ((1<<IRQ1_PIN)|(1<<IRQ2_PIN)|(1<<IRQ3_PIN)|(1<<IRQ4_PIN)|(1<<IRQ5_PIN)|(1<<IRQ7_PIN))

#define TIMEOUT  1000
long timer1=millis()+100;
long timer2=millis()+TIMEOUT;

#define NOT_ACTIVE 7
unsigned char irq_s[8]={NOT_ACTIVE,NOT_ACTIVE,NOT_ACTIVE,NOT_ACTIVE,NOT_ACTIVE,NOT_ACTIVE,NOT_ACTIVE,NOT_ACTIVE};
// Variáveis globais
volatile uint8_t active_irq = NOT_ACTIVE;

#define LED_PIN PB5  // Exemplo: LED no PB5 (ajuste conforme seu hardware)
#define LED_PORT PORTB

// Configuração dos ports
void setup_ports() {
    // Configurar PC0-PC2 como saídas (IPL0-IPL2)
    DDRC |= (1 << IPL0) | (1 << IPL1) | (1 << IPL2) ;
    // VPA inicialmente inativo    
    PORTC |=  (1 << IPL0) | (1 << IPL1) | (1 << IPL2) ;  
    
    // Configurar PB1 como saída (OC1A - Debug) LED
    DDRB |= (1 << PB1)|(1 << PB5)  ;

    // Configura PD0-PD5 como entradas com pull-up
    DDRD &= ~ALL_IRQ_MASK;
    PORTD |= ALL_IRQ_MASK;    
}

/*
  Gerando o sinal de 100HZ no pino PB1
  Usado para gerar interrupção 7 no 68000
*/
void setup_timer1() {
    TCCR1A = (1 << COM1A0);    // Toggle OC1A on compare match
    TCCR1B = (1 << WGM12) | (1 << CS11)  | (1 << CS10);  // CTC mode, prescaler 8
    OCR1A = 1249;              // 1ms period
    TIMSK |= (1 << OCIE1A);    // Habilitar interrupção
}
//Dummy counter, not used
volatile uint32_t ms_counter = 0;
ISR(TIMER1_COMPA_vect) {
  ms_counter++;
  //start_irq(1);  // Gera IRQ nível 6
}

//Timer 2 not used
void setup_timer2() {  // ATMega8 usa Timer2, não Timer0
    // Configurar Timer2 para CTC mode
    TCCR2 = (1 << WGM21);              // CTC mode
    OCR2 = 78;                         // 50us @ 16MHz/8
    TCCR2 |= (1 << CS21);              // Prescaler 8
    TIMSK |= (1 << OCIE2);             // Enable interrupt
}
ISR(TIMER2_COMP_vect) {

}

//int0 not used
void setup_fc_interrupt() {
    // Configurar INT0 para FALLING EDGE (transição 1→0)
    MCUCR |= (1 << ISC01);      // Falling edge generates interrupt  
    MCUCR &= ~(1 << ISC00);     // Clear ISC00 bit
    GICR |= (1 << INT0);        // Enable INT0
}
ISR(INT0_vect) {

}

uint8_t check_irq_pins_status() {
    return (~PIND) & ALL_IRQ_MASK;
}
/*
  To start:
          int7 send 0
          int6 send 1
          int5 send 2
          int4 send 3
          int3 send 4
          int2 send 5
          int1 send 6
       no int  send 7 
*/
uint8_t get_irq_started() {
    uint8_t status = check_irq_pins_status();
    if (status & (1<<IRQ7_PIN)) return 0;
    if (status & (1<<IRQ5_PIN)) return 2;
    if (status & (1<<IRQ4_PIN)) return 3;
    if (status & (1<<IRQ3_PIN)) return 4;
    if (status & (1<<IRQ2_PIN)) return 5;
    if (status & (1<<IRQ1_PIN)) return 6;
    return NOT_ACTIVE;
}

// ✅ Função set and reset IPLx
void set_ipl(uint8_t level) {
  level &= 0x07;
  PORTC = (PORTC & 0xF8) | level;  // Seta nível
  // ⏰ Timing calibrado manualmente
    __asm__ volatile("nop\nnop\nnop\nnop\nnop\nnop\nnop\nnop\nnop\nnop\nnop\nnop");

  PORTC = (PORTC & 0xF8) | NOT_ACTIVE;  // Limpa ANTES do retrigger
  _delay_us(500);
  irq_s[active_irq]=NOT_ACTIVE;
}

void start_irq(uint8_t new_irq){
  if(new_irq == NOT_ACTIVE) return; //excesso de zelo quando estiver funcionando corretamente tirar isso daqui
  if (new_irq < 7 && irq_s[new_irq] == NOT_ACTIVE) {
    active_irq = new_irq;
    irq_s[active_irq]=active_irq;
    set_ipl(active_irq);
  }
}

void setup(){
  Serial.begin(9600);
  Serial.println("Teste do gerenciador de interrupção 1.0"); 
  setup_ports();

  //Setup interrups
  setup_timer1();
  //setup_timer2();

  sei();
  pinMode(LED_BUILTIN, OUTPUT);    
  timer1=millis()+TIMEOUT;
  delay(0.100); // 100 mili segundos
}

void loop() {

  while(1) {
    // 1️⃣ Verificação SÍNCRONA das IRQs
    start_irq(get_irq_started());

    //Activity led
    if ( (millis() > timer1) ){
      timer1=millis()+500;
      LED_PORT ^= (1 << LED_PIN);  // toggle LED
    }
  }
}

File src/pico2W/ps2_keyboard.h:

#ifndef P2_KEYBOARD_H_
#define P2_KEYBOARD_H_
#include "hardware/clocks.h"
#include "hardware/dma.h"
#include "hardware/pio.h"
#include "hardware/gpio.h"
#include "pico/stdlib.h"
#include <stdio.h>
#include <stdlib.h>

#define PS2FREQ   133600.0f

#define PS2_DATA_PIN     16
#define PIRQ             19

// GPIO pins to VIA chip
//enum ps2_pins {PA0=0, PA1, PA2, PA3, PA4, PA5, PA6, PS2_DATA_PIN=15, PS2_CLK_PIN, PIRQ=27};

void initPS2(void);
//unsigned char ps2GetChar(bool auto_print);
//unsigned char ps2GetCharBlk(bool auto_print);
void ps2Task(bool auto_print);

#endif // P2_KEYBOARD_H_
